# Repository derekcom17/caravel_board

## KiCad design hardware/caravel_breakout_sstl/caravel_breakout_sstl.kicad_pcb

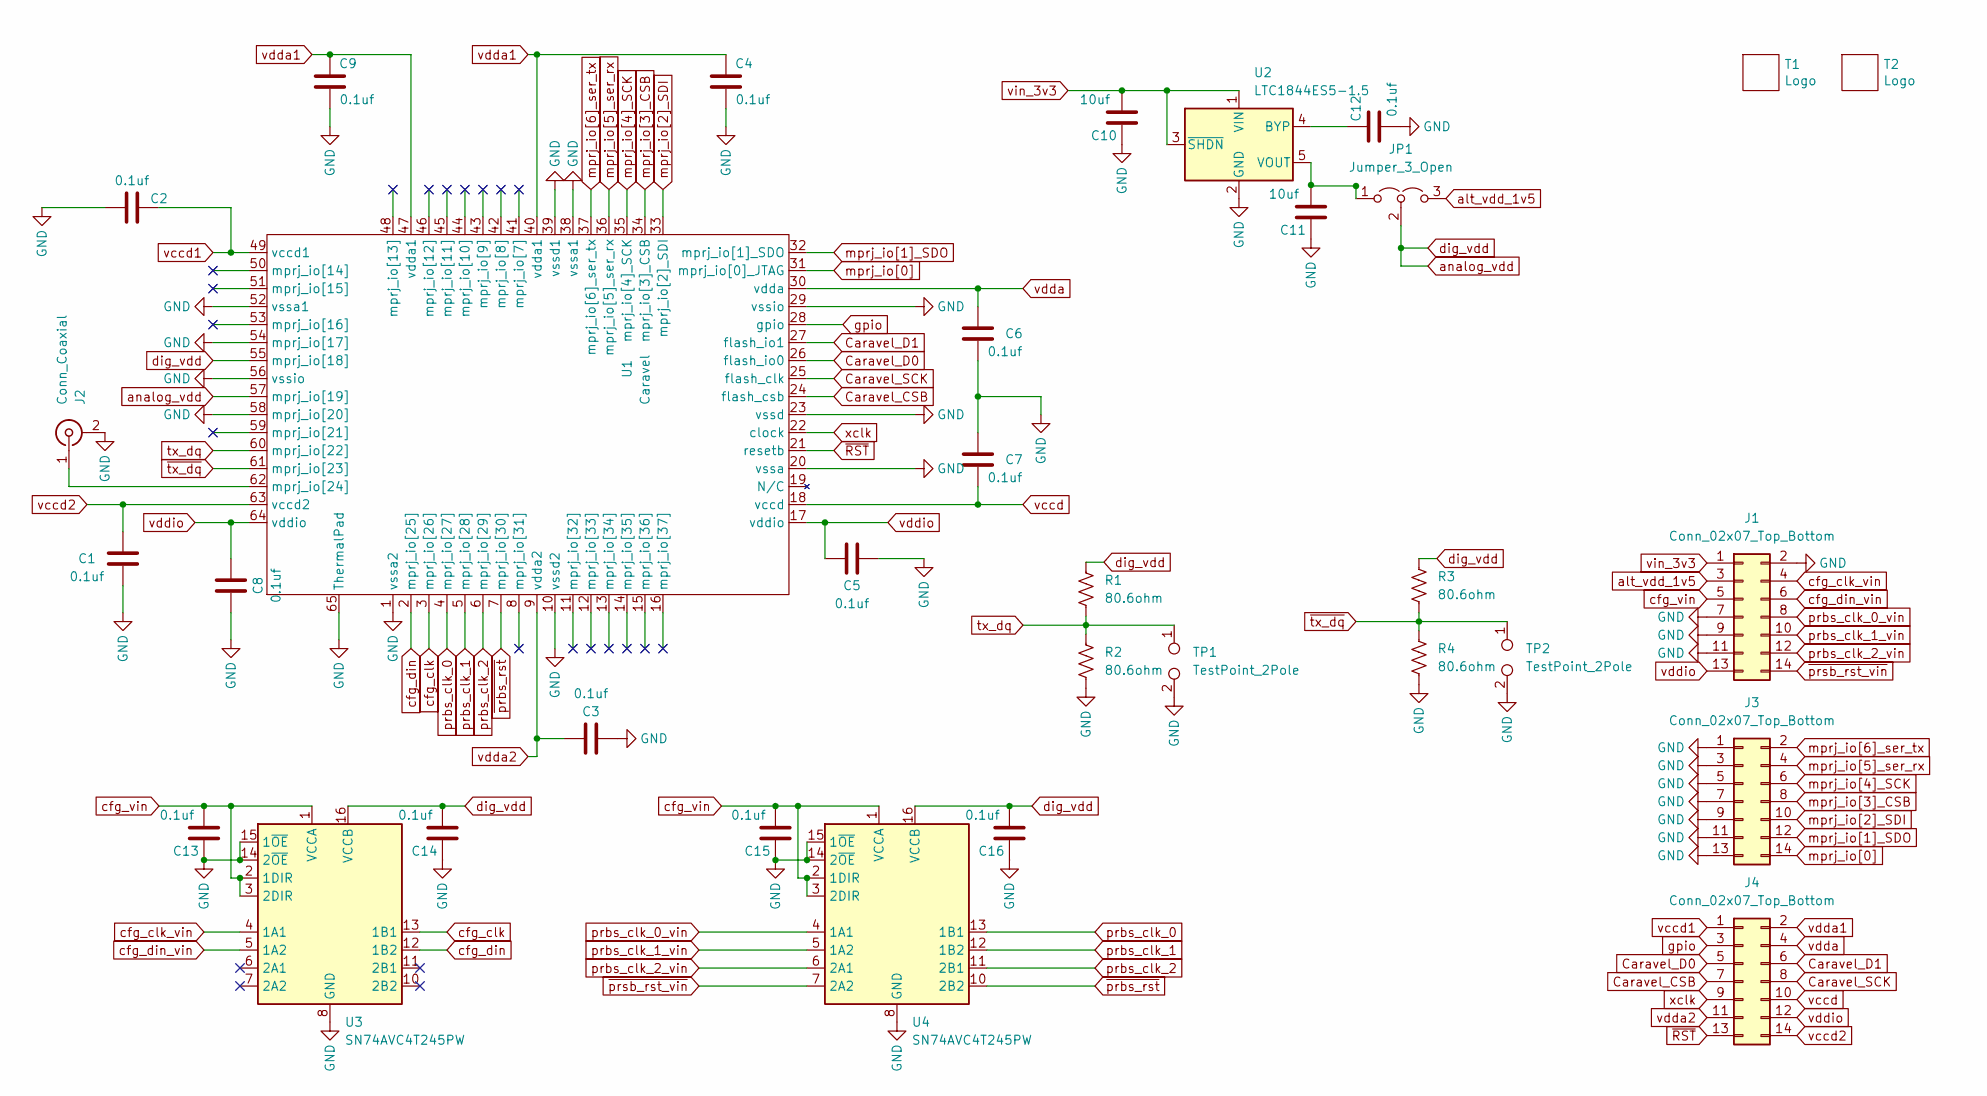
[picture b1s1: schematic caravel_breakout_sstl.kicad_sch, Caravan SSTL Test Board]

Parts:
C1, C2, C3, C4, C5, C6, C7, C8, C9, C12, C13, C14, C15, C16: 0.1uf; C_0402_1005Metric
C10, C11: 10uf; C_0805_2012Metric
J1, J3, J4: Conn_02x07_Top_Bottom; PinSocket_2x07_P2.54mm_Vertical
J2: Conn_Coaxial; SMA_Amphenol_132134-16_Vertical
JP1: Jumper_3_Open; PinHeader_1x03_P2.54mm_Vertical
R1, R2, R3, R4: 80.6ohm; R_0402_1005Metric
T1: Logo; logo_small
T2: Logo; ef_logo
TP1, TP2: TestPoint_2Pole; TestPoint_2Pads_Pitch2.54mm_Drill0.8mm
U1: Caravel; QFN-64-1EP_9x9mm_P0.5mm_EP6x6mm
U2: LTC1844ES5-1.5; TSOT-23-5
U3, U4: SN74AVC4T245PW; Texas_R-PDSO-G16

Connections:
Caravel_CSB: J4.7, U1.24 (flash_csb)
Caravel_D0: J4.5, U1.26 (flash_io0)
Caravel_D1: J4.6, U1.27 (flash_io1)
Caravel_SCK: J4.8, U1.25 (flash_clk)
GND: C1.1, C2.1, C3.2, C4.2, C5.1, C6.2, C7.1, C8.1, C9.2, C10.1, C11.1, C12.2, C13.1, C14.1, C15.1, C16.1, J1.2, J1.7, J1.9, J1.11, J2.2 (Ext), J3.1, J3.3, J3.5, J3.7, J3.9, J3.11, J3.13, R2.2, R4.2, TP1.2, TP2.2, U1.1 (vssa2), U1.10 (vssd2), U1.20 (vssa), U1.23 (vssd), U1.29 (vssio), U1.38 (vssa1), U1.39 (vssd1), U1.52 (vssa1), U1.54 (mprj_io[17]), U1.56 (vssio), U1.58 (mprj_io[20]), U1.65 (ThermalPad), U2.2 (GND), U3.8 (GND), U3.9 (GND), U3.14 (2~OE), U3.15 (1~OE), U4.8 (GND), U4.9 (GND), U4.14 (2~OE), U4.15 (1~OE)
unnamed: C11.2, JP1.1 (A), U2.5 (VOUT)
unnamed: C12.1, U2.4 (BYP)
unnamed: J2.1 (In), U1.62 (mprj_io[24])
alt_vdd_1v5: J1.3, JP1.3 (B)
analog_vdd: C14.2, C16.2, JP1.2 (C), R1.1, R3.1, U1.55 (mprj_io[18]), U1.57 (mprj_io[19]), U3.16 (VCCB), U4.16 (VCCB)
cfg_clk: U1.3 (mprj_io[26]), U3.13 (1B1)
cfg_clk_vin: J1.4, U3.4 (1A1)
cfg_din: U1.2 (mprj_io[25]), U3.12 (1B2)
cfg_din_vin: J1.6, U3.5 (1A2)
cfg_vin: C13.2, C15.2, J1.5, U3.1 (VCCA), U3.2 (1DIR), U3.3 (2DIR), U4.1 (VCCA), U4.2 (1DIR), U4.3 (2DIR)
gpio: J4.3, U1.28 (gpio)
mprj_io[0]: J3.14, U1.31 (mprj_io[0]_JTAG)
mprj_io[1]_SDO: J3.12, U1.32 (mprj_io[1]_SDO)
mprj_io[2]_SDI: J3.10, U1.33 (mprj_io[2]_SDI)
mprj_io[3]_CSB: J3.8, U1.34 (mprj_io[3]_CSB)
mprj_io[4]_SCK: J3.6, U1.35 (mprj_io[4]_SCK)
mprj_io[5]_ser_rx: J3.4, U1.36 (mprj_io[5]_ser_rx)
mprj_io[6]_ser_tx: J3.2, U1.37 (mprj_io[6]_ser_tx)
prbs_clk_0: U1.4 (mprj_io[27]), U4.13 (1B1)
prbs_clk_0_vin: J1.8, U4.4 (1A1)
prbs_clk_1: U1.5 (mprj_io[28]), U4.12 (1B2)
prbs_clk_1_vin: J1.10, U4.5 (1A2)
prbs_clk_2: U1.6 (mprj_io[29]), U4.11 (2B1)
prbs_clk_2_vin: J1.12, U4.6 (2A1)
tx_dq: R1.2, R2.1, TP1.1, U1.60 (mprj_io[22])
vccd: C7.2, J4.10, U1.18 (vccd)
vccd1: C2.2, J4.1, U1.49 (vccd1)
vccd2: C1.2, J4.14, U1.63 (vccd2)
vdda: C6.1, J4.4, U1.30 (vdda)
vdda1: C4.1, C9.1, J4.2, U1.40 (vdda1), U1.47 (vdda1)
vdda2: C3.1, J4.11, U1.9 (vdda2)
vddio: C5.2, C8.2, J1.13, J4.12, U1.17 (vddio), U1.64 (vddio)
vin_3v3: C10.2, J1.1, U2.1 (VIN), U2.3 (~SHDN)
xclk: J4.9, U1.22 (clock)
~RST: J4.13, U1.21 (resetb)
~prbs_rst: U1.7 (mprj_io[30]), U4.10 (2B2)
~prsb_rst_vin: J1.14, U4.7 (2A2)
~tx_dq: R3.2, R4.1, TP2.1, U1.61 (mprj_io[23])

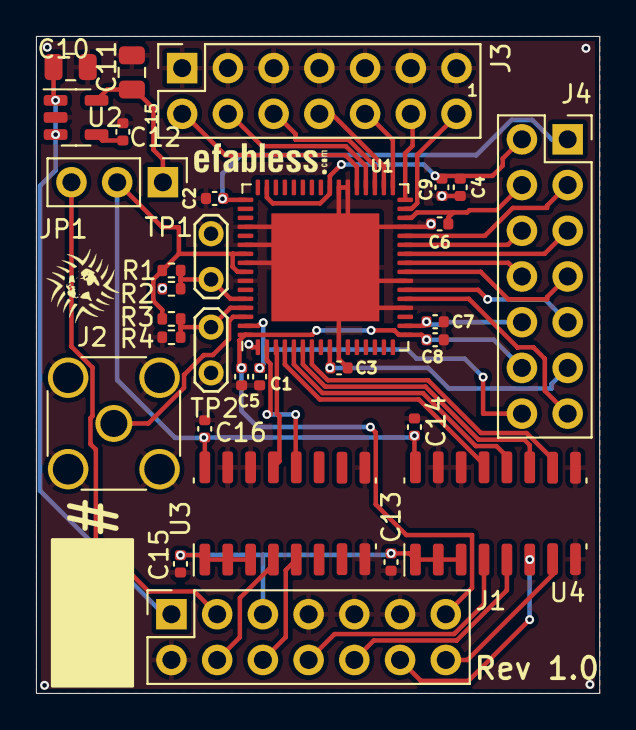
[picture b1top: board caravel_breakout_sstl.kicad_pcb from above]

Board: 2 copper layers, 31.3 x 36.5 mm, 33 parts (0 on the bottom side), 43 nets.

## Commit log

2022-06-15 Initial commit
    Copy breakout board project and disconnect some unused Caravel pins
2022-06-22 Finish first draft of schematic
2022-06-22 Update schematic
    * Add new connectors
    * Add some caps
    * Add alternate power jumper
2022-06-22 Minor fixes
2022-07-05 Finish draft of Layout
2022-07-05 Add logos to back
2022-07-07 Minor updates to improve routing
    Ground all unused pins
